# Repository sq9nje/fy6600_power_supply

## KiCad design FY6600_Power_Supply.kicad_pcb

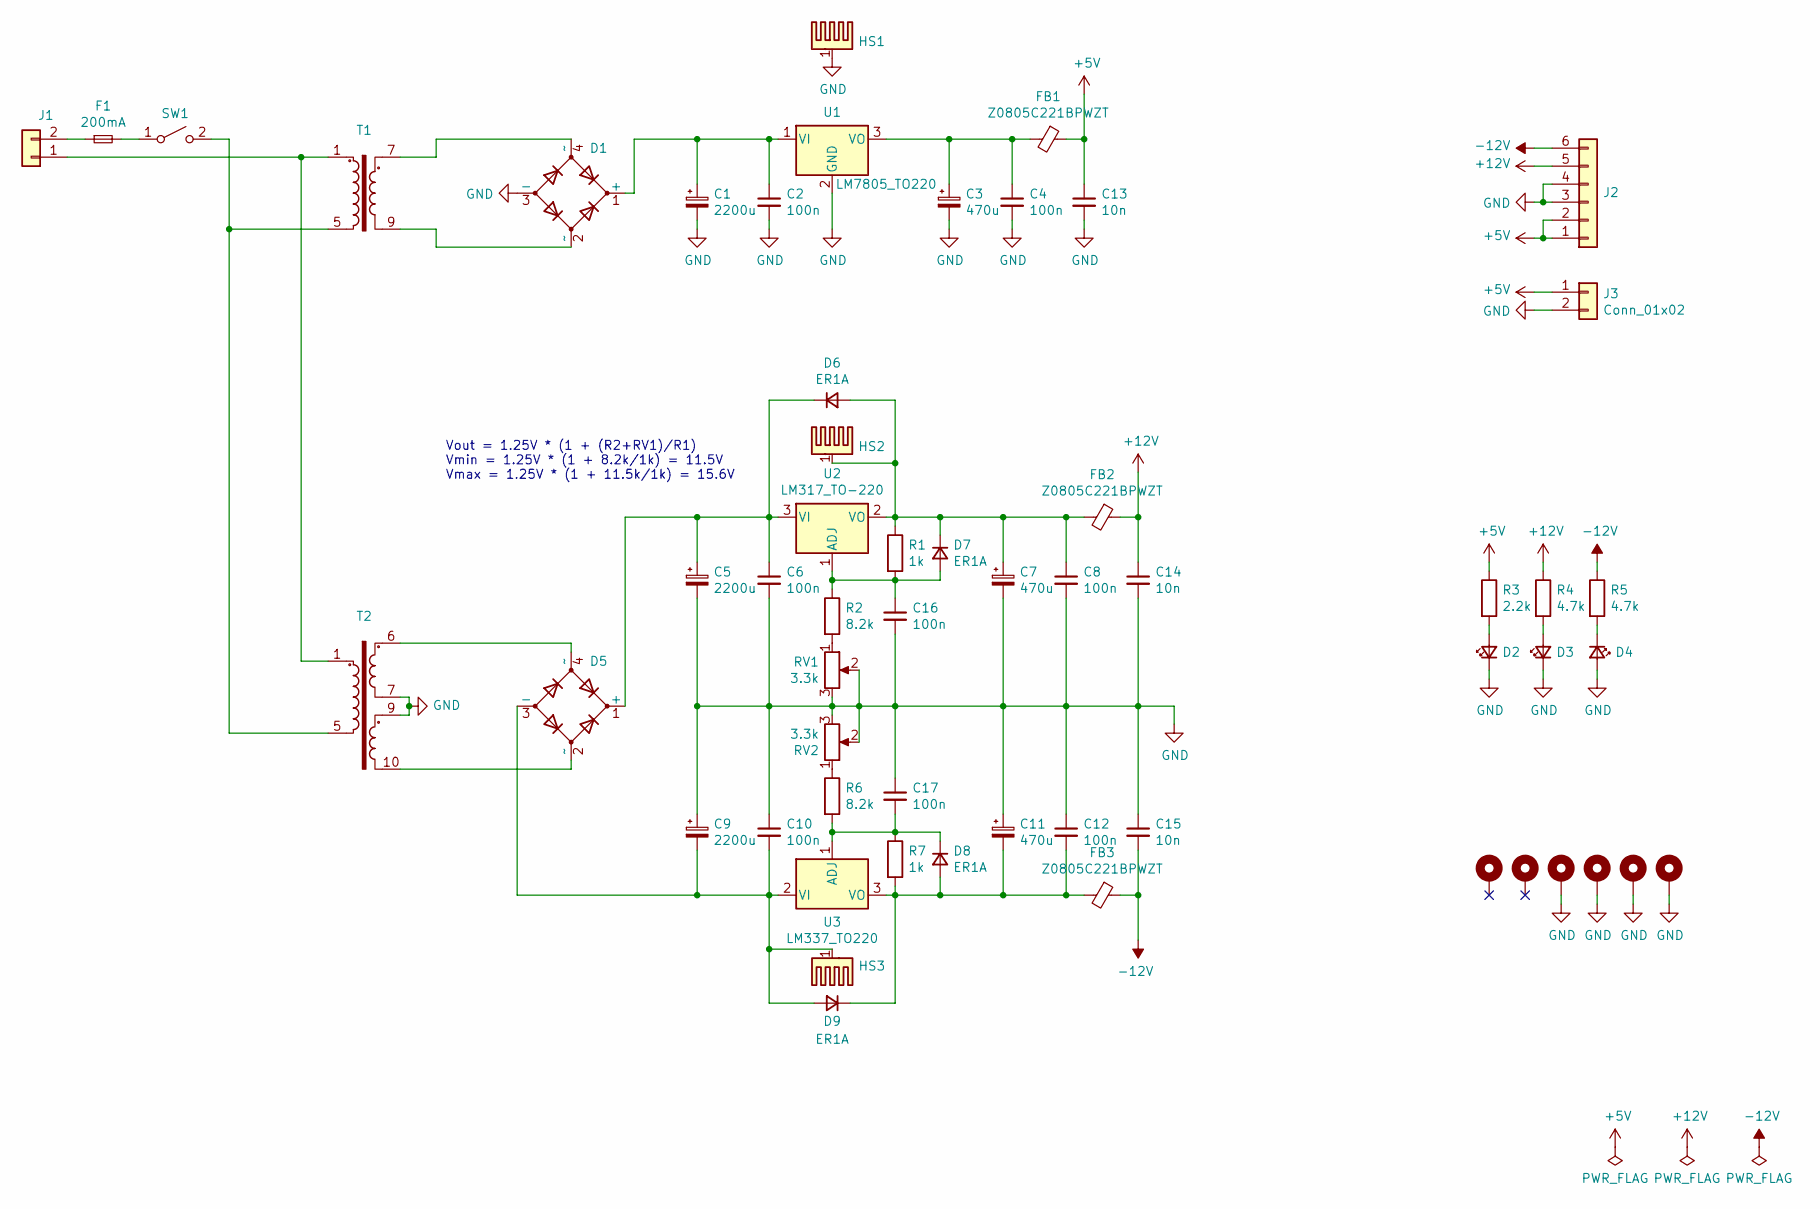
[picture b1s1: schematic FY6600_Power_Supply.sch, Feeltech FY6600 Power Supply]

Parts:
C1, C5, C9: 2200u; CP_Radial_D18.0mm_P7.50mm
C2, C4, C6, C8, C10, C12, C16, C17: 100n; C_0805_2012Metric_Pad1.18x1.45mm_HandSolder
C3, C7, C11: 470u; CP_Radial_D10.0mm_P5.00mm
C13, C14, C15: 10n; C_0805_2012Metric_Pad1.18x1.45mm_HandSolder
D1, D5: D_Bridge_+A-A; Diode_Bridge_Round_D9.0mm
D2, D3, D4: LED_Small; D_0805_2012Metric_Pad1.15x1.40mm_HandSolder
D6, D7, D8, D9: ER1A; D_SMA
F1: 200mA; Fuseholder_Cylinder-5x20mm_Stelvio-Kontek_PTF78_Horizontal_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
FB1, FB2, FB3: Z0805C221BPWZT; R_0805_2012Metric_Pad1.20x1.40mm_HandSolder
H1, H2, H3, H4, H5, H6: MountingHole_Pad; MountingHole_3.2mm_M3_DIN965_Pad
HS1, HS2, HS3: Heatsink_Pad; TestPoint_THTPad_2.5x2.5mm_Drill1.2mm
J1: Conn_01x02; TerminalBlock_Wuerth_691311400102_P7.62mm
J2: Conn_01x06; JST_XH_B6B-XH-A_1x06_P2.50mm_Vertical
J3: Conn_01x02; JST_XH_B2B-XH-A_1x02_P2.50mm_Vertical
R1, R7: 1k; R_0805_2012Metric_Pad1.20x1.40mm_HandSolder
R2, R6: 8.2k; R_0805_2012Metric_Pad1.20x1.40mm_HandSolder
R3: 2.2k; R_0805_2012Metric_Pad1.20x1.40mm_HandSolder
R4, R5: 4.7k; R_0805_2012Metric_Pad1.20x1.40mm_HandSolder
RV1, RV2: 3.3k; Potentiometer_Piher_PT-6-V_Vertical
SW1: SW_SPST; TerminalBlock_Wuerth_691311400102_P7.62mm
T1: Transformer_1P_1S; Transformer_Breve_TEZ-38x45
T2: Transformer_1P_2S; Transformer_Breve_TEZ-38x45
U1: LM7805_TO220; TO-220-3_Vertical
U2: LM317_TO-220; TO-220-3_Vertical
U3: LM337_TO220; TO-220-3_Vertical

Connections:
+5V: C13.1, FB1.1, J2.1, J2.2, J3.1, R3.1
+12V: C14.1, FB2.1, J2.5, R4.1
-12V: C15.2, FB3.1, J2.6, R5.1
GND: C1.2, C2.2, C3.2, C4.2, C5.2, C6.2, C7.2, C8.2, C9.1, C10.1, C11.1, C12.1, C13.2, C14.2, C15.1, C16.2, C17.1, D1.3 (-), D2.1 (K), D3.1 (K), D4.2 (A), H3.1, H4.1, H5.1, H6.1, HS1.1, J2.3, J2.4, J3.2, RV1.2, RV1.3, RV2.2, RV2.3, T2.7, T2.9, U1.2 (GND)
unnamed: C1.1, C2.1, D1.1 (+), U1.1 (VI)
unnamed: C3.1, C4.1, FB1.2, U1.3 (VO)
unnamed: C5.1, C6.1, D5.1 (+), D6.1 (K), U2.3 (VI)
unnamed: C7.1, C8.1, D6.2 (A), D7.1 (K), FB2.2, HS2.1, R1.1, U2.2 (VO)
unnamed: C9.2, C10.2, D5.3 (-), D9.2 (A), HS3.1, U3.2 (VI)
unnamed: C11.2, C12.2, D8.2 (A), D9.1 (K), FB3.2, R7.2, U3.3 (VO)
unnamed: C16.1, D7.2 (A), R1.2, R2.1, U2.1 (ADJ)
unnamed: C17.2, D8.1 (K), R6.2, R7.1, U3.1 (ADJ)
unnamed: D1.2 (~~), T1.9
unnamed: D1.4 (~~), T1.7
unnamed: D2.2 (A), R3.2
unnamed: D3.2 (A), R4.2
unnamed: D4.1 (K), R5.2
unnamed: D5.2 (~~), T2.10
unnamed: D5.4 (~~), T2.6
unnamed: F1.1, J1.2
unnamed: F1.2, SW1.1 (A)
unnamed: J1.1, T1.1, T2.1
unnamed: R2.2, RV1.1
unnamed: R6.1, RV2.1
unnamed: SW1.2 (B), T1.5, T2.5

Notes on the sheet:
Vout = 1.25V * (1 + (R2+RV1)/R1) Vmin = 1.25V * (1 + 8.2k/1k) = 11.5V Vmax = 1.25V * (1 + 11.5k/1k) = 15.6V

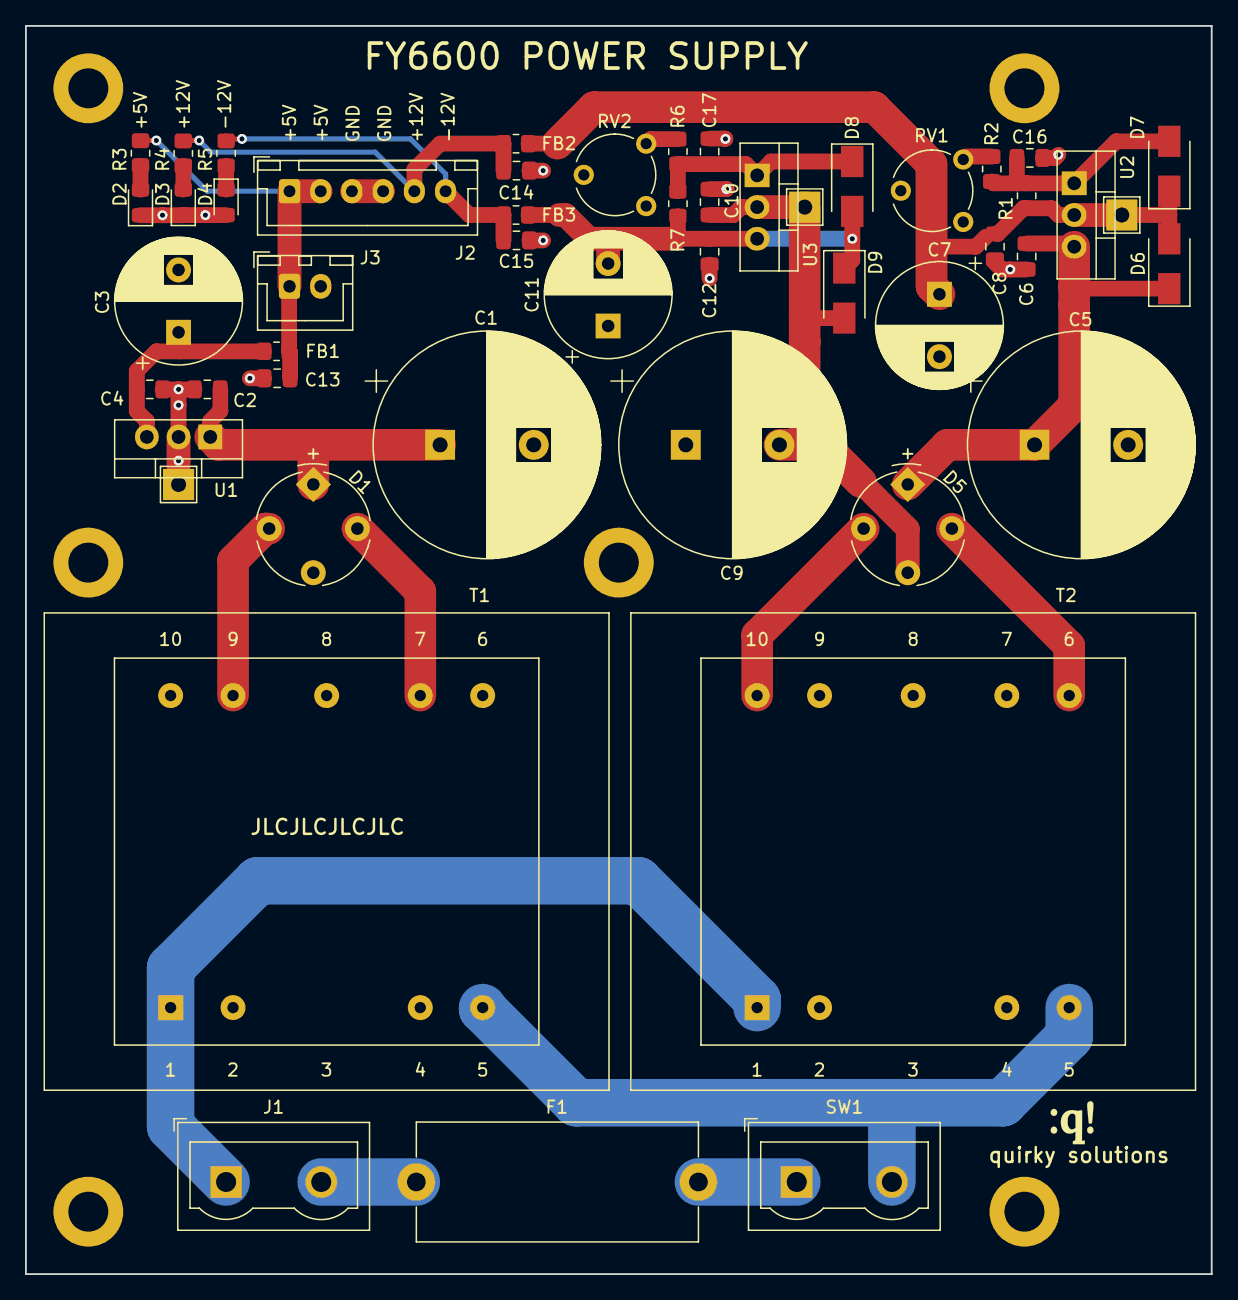
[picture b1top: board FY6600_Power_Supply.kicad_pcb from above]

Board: 2 copper layers, 95.0 x 100.0 mm, 58 parts (0 on the bottom side), 25 nets.

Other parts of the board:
Ref**: Val**; qs_logo

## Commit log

2021-01-30 FY6600 Power Supply
2021-02-20 Interactive BOM
